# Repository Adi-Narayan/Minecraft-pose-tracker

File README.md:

Python script to play Minecraft without using a mouse or a keyboard.
This script uses OpenCV to track body poses, using the mediapipe library and translates it on the game.

Execute the Minepose.py to move forwards, jump and strafe left or right.
Execute main_ref.py to play Minecraft properly with player movements, mouse movements, block-breaking movements and crouch.

Squat to crouch.
Either hand up to turn mouse in the corresponding direction.
Hold your hands in a prayer pose and move them up or down together to turn the camera up or down.
Raise Right leg up but just below the knee to walk forwards.
Raise Left leg up to jump sprint.

TURN RAW INPUT OFF FOR MOUSE SETTINGS WHEN YOU OPEN MINECRAFT!!!

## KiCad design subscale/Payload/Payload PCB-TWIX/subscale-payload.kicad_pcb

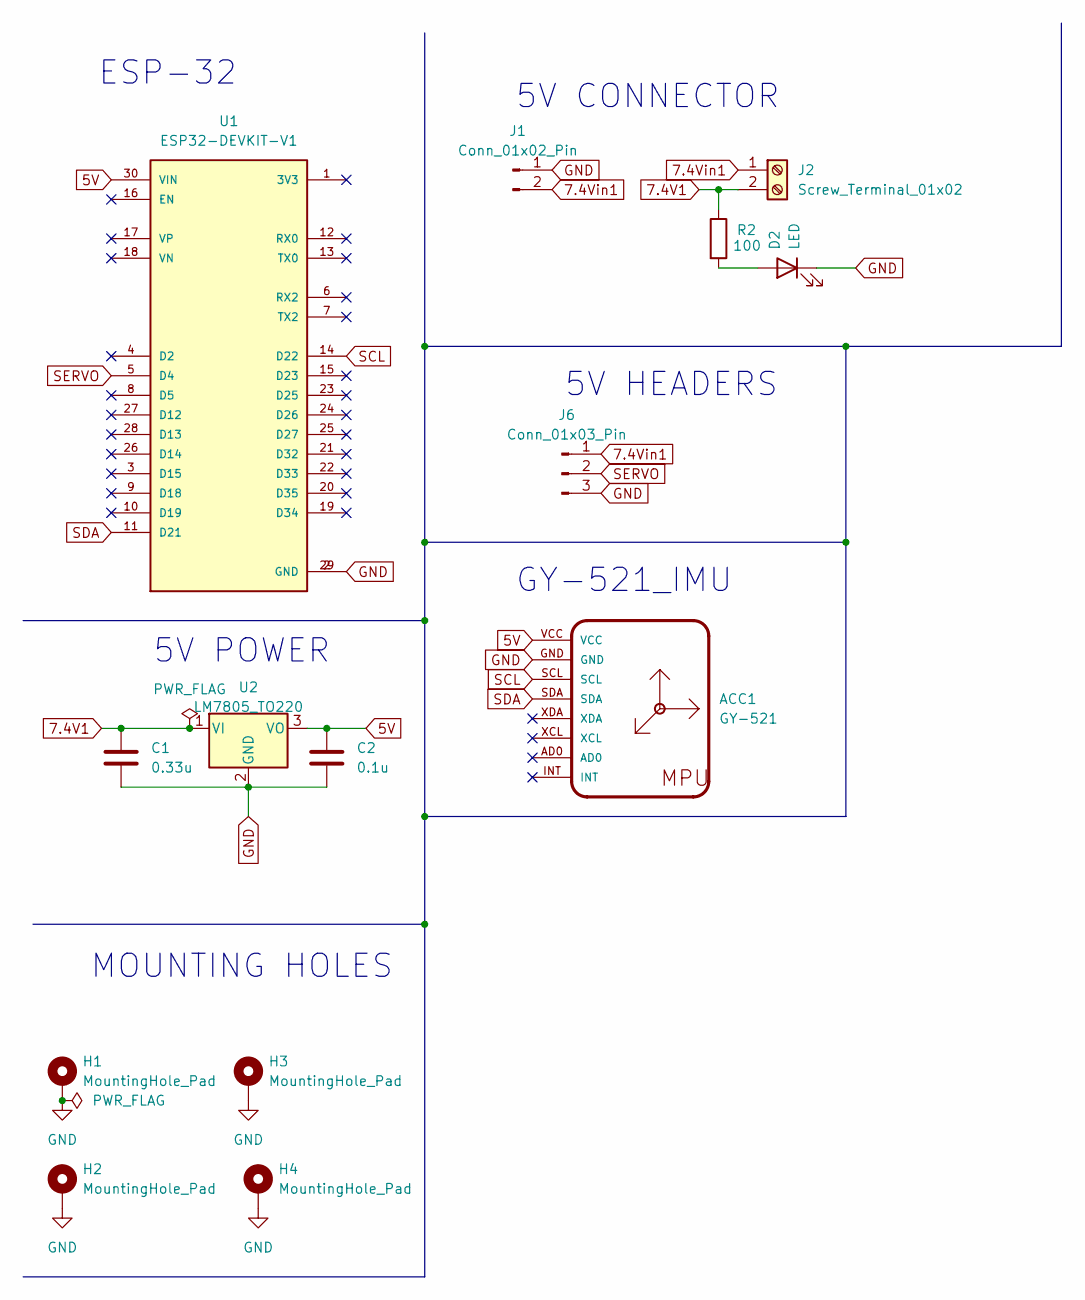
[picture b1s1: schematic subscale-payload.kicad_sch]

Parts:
ACC1: GY-521
C1: 0.33u; C_0805_2012Metric
C2: 0.1u; C_0805_2012Metric
D2: LED; LED_0805_2012Metric
H1, H2, H3, H4: MountingHole_Pad; MountingHole_4.3mm_M4_DIN965_Pad
J1: Conn_01x02_Pin; AMASS_XT60-F_1x02_P7.20mm_Vertical
J2: Screw_Terminal_01x02; TerminalBlock_bornier-2_P5.08mm
J6: Conn_01x03_Pin; PinHeader_1x03_P1.00mm_Vertical
R2: 100; R_0805_2012Metric
U1: ESP32-DEVKIT-V1; esp32wroom
U2: LM7805_TO220; TO-220-3_Vertical

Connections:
5V: ACC1.VCC, C2.1, U1.30 (VIN), U2.3 (VO)
7.4V1: C1.1, J2.2, R2.1, U2.1 (VI)
7.4Vin1: J1.2, J2.1, J6.1
GND: ACC1.GND, C1.2, C2.2, D2.1 (K), H1.1, H2.1, H3.1, H4.1, J1.1, J6.3, U1.2 (GND), U1.29 (GND), U2.2 (GND)
unnamed: D2.2 (A), R2.2
SCL: ACC1.SCL, U1.14 (D22)
SDA: ACC1.SDA, U1.11 (D21)
SERVO: J6.2, U1.5 (D4)

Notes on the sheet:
MOUNTING HOLES
GY-521_IMU
5V HEADERS
ESP-32
5V POWER
5V CONNECTOR

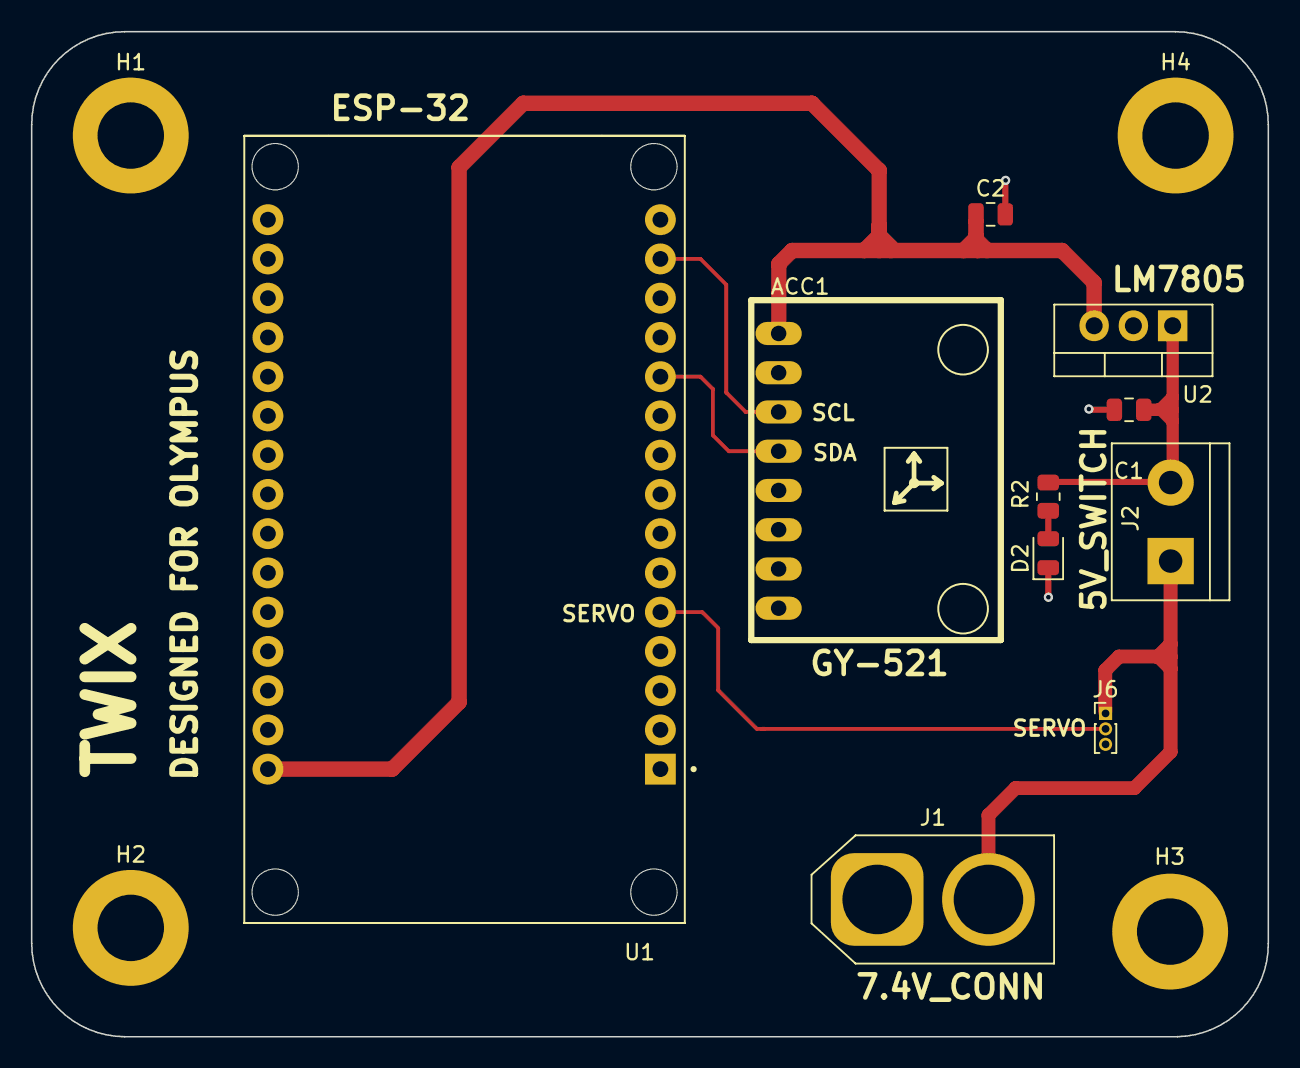
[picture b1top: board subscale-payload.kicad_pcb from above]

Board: 2 copper layers, 80.0 x 65.0 mm, 14 parts (0 on the bottom side), 8 nets.

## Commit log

2024-10-28 Spring tester code added
2025-02-18 Payload Docs for Subscale 2025
